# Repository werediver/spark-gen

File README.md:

# Spark generator for microphone calibration

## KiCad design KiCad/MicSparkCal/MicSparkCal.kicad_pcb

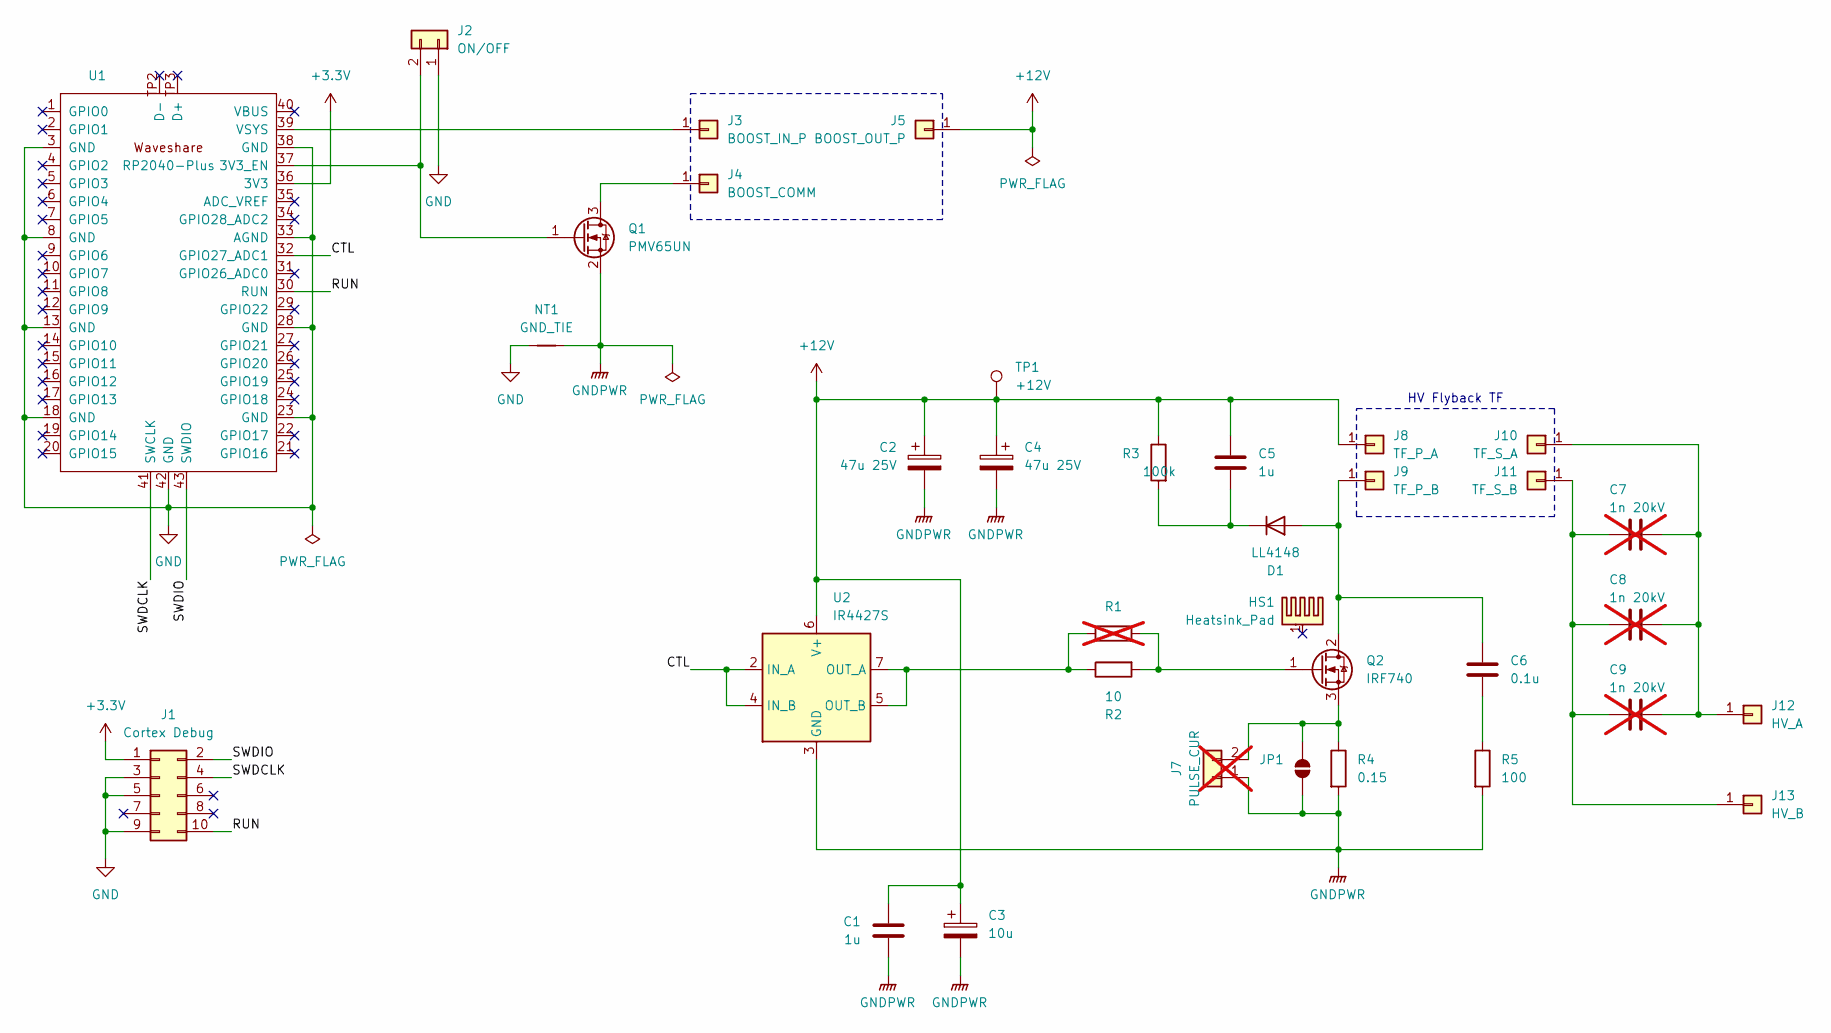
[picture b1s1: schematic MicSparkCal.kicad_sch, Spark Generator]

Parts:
C1, C5: 1u; C_0805_2012Metric_Pad1.18x1.45mm_HandSolder
C2, C4: 47u 25V; CP_EIA-7343-31_Kemet-D_Pad2.25x2.55mm_HandSolder
C3: 10u; CP_EIA-3216-10_Kemet-I_Pad1.58x1.35mm_HandSolder
C6: 0.1u; C_0805_2012Metric_Pad1.18x1.45mm_HandSolder
C7, C8, C9: 1n 20kV; C_Rect_L16.5mm_W4.7mm_P15.00mm_MKT; not fitted
D1: LL4148; D_MiniMELF
HS1: Heatsink_Pad; HeatSink_TO-220
J1: Cortex Debug; PinHeader_2x05_P1.27mm_Vertical_SMD
J2: ON/OFF; Molex_KK-254_AE-6410-02A_1x02_P2.54mm_Vertical
J3: BOOST_IN_P; PinHeader_1x01_P2.54mm_Vertical
J4: BOOST_COMM; PinHeader_1x01_P2.54mm_Vertical
J5: BOOST_OUT_P; PinHeader_1x01_P2.54mm_Vertical
J7: PULSE_CUR; PinHeader_1x02_P2.54mm_Vertical; not fitted
J8: TF_P_A; PinHeader_1x01_P2.54mm_Vertical
J9: TF_P_B; PinHeader_1x01_P2.54mm_Vertical
J10: TF_S_A; PinHeader_1x01_P2.54mm_Vertical
J11: TF_S_B; PinHeader_1x01_P2.54mm_Vertical
J12: HV_A; PinHeader_1x01_P2.54mm_Vertical
J13: HV_B; PinHeader_1x01_P2.54mm_Vertical
JP1: SolderJumper-2_P1.3mm_Open_RoundedPad1.0x1.5mm
NT1: GND_TIE; NetTie-2_SMD_Pad2.0mm
Q1: PMV65UN; SOT-23
Q2: IRF740; TO-220-3_Vertical
R1: R_0805_2012Metric_Pad1.20x1.40mm_HandSolder; not fitted
R2: 10; R_0805_2012Metric_Pad1.20x1.40mm_HandSolder
R3: 100k; R_0805_2012Metric_Pad1.20x1.40mm_HandSolder
R4: 0.15; R_2512_6332Metric
R5: 100; R_0805_2012Metric_Pad1.20x1.40mm_HandSolder
TP1: +12V; TestPoint_Pad_D1.5mm
U1: RP2040-Plus; Waveshare_RP2040-Plus_SMD
U2: IR4427S; SOIC-8_3.9x4.9mm_P1.27mm

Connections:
+3.3V: J1.1, U1.36 (3V3)
+12V: C1.1, C2.1, C3.1, C4.1, C5.1, J5.1, J8.1, R3.1, TP1.1, U2.6 (V+)
/CTL: U1.32 (GPIO27_ADC1), U2.2 (IN_A), U2.4 (IN_B)
/RUN: J1.10, U1.30 (RUN)
/SWDCLK: J1.4, U1.41 (SWCLK)
/SWDIO: J1.2, U1.43 (SWDIO)
GND: J1.3, J1.5, J1.9, J2.1, NT1.1, U1.3 (GND), U1.8 (GND), U1.13 (GND), U1.18 (GND), U1.23 (GND), U1.28 (GND), U1.33 (AGND), U1.38 (GND), U1.42 (GND)
GNDPWR: C1.2, C2.2, C3.2, C4.2, J7.1, JP1.1 (A), NT1.2, Q1.2 (S), R4.2, R5.2, U2.3 (GND)
unnamed: C6.2, R5.1
unnamed: C6.1, D1.2 (A), J9.1, Q2.2 (D)
unnamed: C5.2, D1.1 (K), R3.2
unnamed: J2.2, Q1.1 (G), U1.37 (3V3_EN)
unnamed: J3.1, U1.39 (VSYS)
unnamed: J4.1, Q1.3 (D)
unnamed: J7.2, JP1.2 (B), Q2.3 (S), R4.1
unnamed: C7.2, C8.2, C9.2, J10.1, J12.1
unnamed: C7.1, C8.1, C9.1, J11.1, J13.1
unnamed: Q2.1 (G), R1.2, R2.2
unnamed: R1.1, R2.1, U2.5 (OUT_B), U2.7 (OUT_A)

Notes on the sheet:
HV Flyback TF

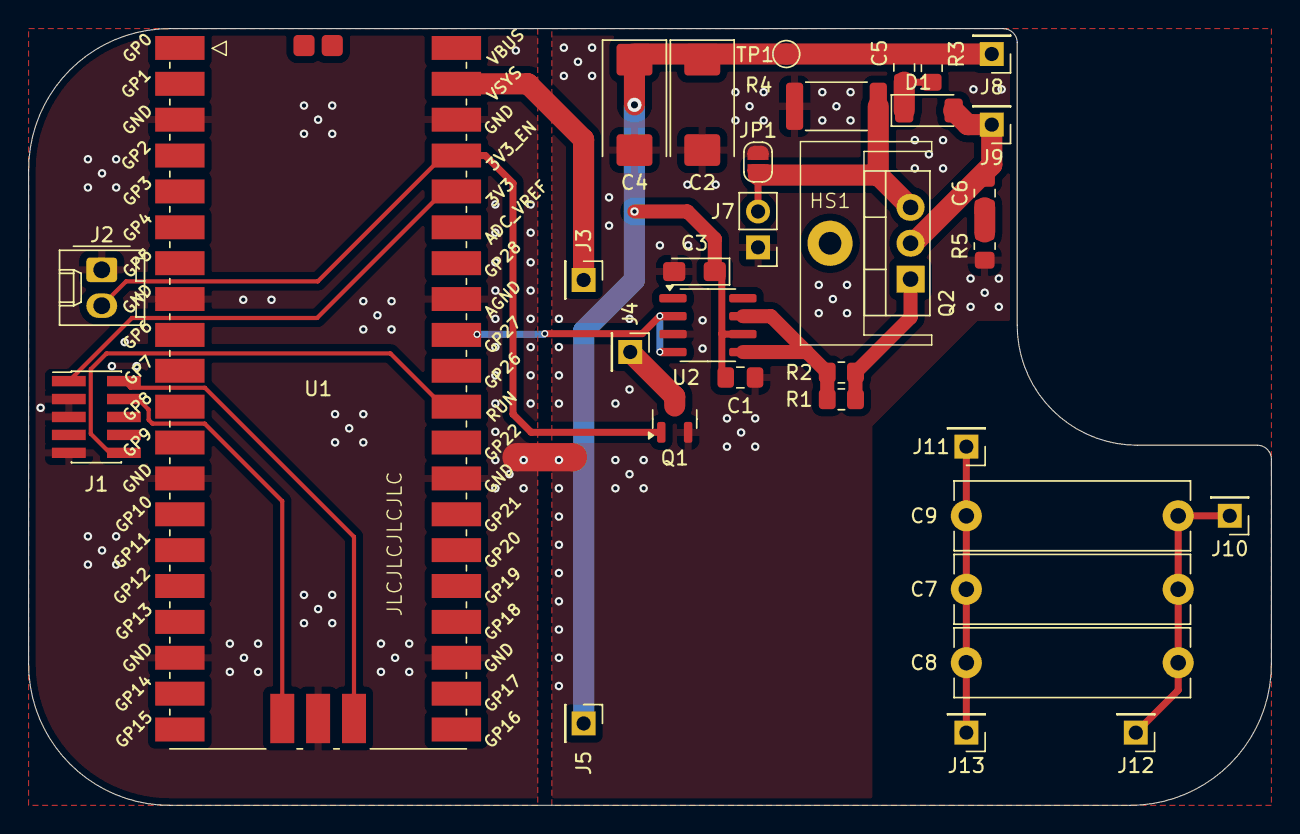
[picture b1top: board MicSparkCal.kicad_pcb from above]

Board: 2 copper layers, 88.0 x 55.0 mm, 35 parts (0 on the bottom side), 19 nets.

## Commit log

2024-06-10 Add the first revision of the spark generator h/w
2024-06-10 Add ".gitignore"
2024-06-10 Add a (rudimentary) README
2024-06-10 Set h/w revision to 2 and include some fixes
